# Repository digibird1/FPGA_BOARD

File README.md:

# FPGA_BOARD
Eagle design files of a two layer PCB for the ALTERA EP3C5E144 FPGA, including a FTDI USB2.0 controller, 2x 80 MSPS ADC, GPIO, JTAG, configuration FLASH 

https://www.altera.com/en_US/pdfs/literature/hb/cyc3/cyclone3_handbook.pdf

http://www.analog.com/media/en/technical-documentation/data-sheets/AD9057.pdf

http://www.ftdichip.com/Products/ICs/FT232H.htm

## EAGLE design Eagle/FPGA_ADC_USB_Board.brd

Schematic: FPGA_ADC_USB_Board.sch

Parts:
C1, C5, C7, C9, C11, C12, C13: 0.1u; C0805
C2, C3: 27p; C0805
C4, C8, C10: 47u; C0805
C6, C15: 0.1; C0805
C14: 10n; C0805
C16, C17, C18, C19, C20, C21, C22, C23, C24, C25, C26, C27, C28, C29, C30, C31, C32, C33, C34, C35, C36, C37, C38, C39, C41, C44, C47, C49, C53, C54, C55, C56, C59, C60, C61: 100n; C0805
C40, C42, C43, C45, C46, C48, C52: 10u; C0805
C50, C51, C57, C58: 100nF; C0805
C62: 1u; C0805
CONFIG_FLASH: EPCS-FALSH; SO08
D1, D2: BAV99; SOT23
D3, D4, D5: PMEG2010AEH; SOD123
EXT_5V: PINHD-1X2; 1X02
IC1: EP3C5E144-V2; EQFP144
IC2: 74LVC1G07DBV; SOT23-5
JTAG: PINHD-2X5; 2X05
L1, L2: 600R/0.5A; R0805
L3, L4, L5, L6, L7: MH2029-300Y; R0805
LED1: Yellow; R0805
LED2: Green; R0805
LED_1, LED_2, LED_3, LED_4: LED_ELED_0805; R0805
LS: 3.3V; SOT223
OSCILLATOR50_MHZ: 636L3I050M00000; OSZI_5X3.2
POWER_SELECT: PINHD-1X3; 1X03
Q1: 12MHz; QS
R1: 12k/1%; M0805
R2, R6, R7, R8: 10k; M0805
R3, R4: 0; M0805
R5: 2k; M0805
R9, R10: 470; M0805
R11: 27; M0805
R12: 24.9; R0805
R13, R14, R15, R17, R18: 10k; R0805
R16: 1k; R0805
R19, R30: 50Ohm; R0805
R20, R21, R22, R23, R24, R25: 0; R0805
R26, R27, R28, R29: 330; R0805
R31: 100k; R0805
R33: 120; R0805
S1: 10-XX; B3F-10XX
U$1: FT232H; LQFP48
U$2, U$6: AD9057; SSOP20
U$3: 93LC56; DIL-08
U$4: 2.5V; SOT223
U$5: 1.2V; SOT223
U$7: FPGA_GPIO_DE0; 2X20
U$8: NET_TIE; NET-TIE
X1: PN61729-S
X2, X3: BU-SMA-V

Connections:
1.2V: C16.1, C17.1, C18.1, C19.1, C20.1, C21.1, C22.1, C23.1, C36.1, C37.1, C48.1, IC1.5 (VCCINT), IC1.29 (VCCINT), IC1.37 (VCCD_PLL), IC1.45 (VCCINT), IC1.61 (VCCINT), IC1.78 (VCCINT), IC1.102 (VCCINT), IC1.109 (VCCD_PLL), IC1.116 (VCCINT), IC1.134 (VCCINT), U$5.2 (OUT), U$5.4 (OUT)
2.5V: C38.1, C39.1, C45.1, IC1.35 (VCCA), IC1.107 (VCCA), JTAG.4, R17.2, R18.2, R20.2, R22.2, R24.2, U$4.2 (OUT), U$4.4 (OUT)
3.3V: C4.1, C5.1, C11.1, C12.1, C13.1, C15.1, C24.1, C25.1, C26.1, C27.1, C28.1, C29.1, C30.1, C31.1, C32.1, C33.1, C34.1, C35.1, C42.1, C54.1, C59.1, CONFIG_FLASH.3 (VCC), CONFIG_FLASH.7 (VCC1), CONFIG_FLASH.8 (VCC2), D1.2 (C2), D2.2 (C2), IC1.17 (VCCIO), IC1.26 (VCCIO), IC1.40 (VCCIO), IC1.47 (VCCIO), IC1.56 (VCCIO), IC1.62 (VCCIO), IC1.81 (VCCIO), IC1.93 (VCCIO), IC1.117 (VCCIO), IC1.122 (VCCIO), IC1.130 (VCCIO), IC1.139 (VCCIO), IC2.5 (VCC), L1.1, L2.1, L6.1, LS.2 (OUT), LS.4 (OUT), R2.2, R6.2, R7.2, R8.2, R9.2, R10.2, R13.2, R14.2, R15.2, R31.2, U$1.12 (VCCIO), U$1.24 (VCCIO2), U$1.39 (VCCD), U$1.40 (VREGIN), U$1.46 (VCCIO3), U$2.15 (V_DD), U$3.8 (VCC), U$6.15 (V_DD), U$7.29 (3.3V)
5V: L3.1, L4.1, L5.1, L7.1, POWER_SELECT.2
5V_ANALOG: C52.1, C53.1, C55.1, C56.1, C60.1, C61.1, L7.2, U$2.5 (V_D1), U$2.8 (V_D2), U$6.5 (V_D1), U$6.8 (V_D2)
5V_EXT: D3.1 (A), POWER_SELECT.1
5V_USB: D5.2 (C), U$7.11 (5V), X1.1
ACBUS0: IC1.50 (IO50), U$1.21 (ACBUS0)
ACBUS1: IC1.44 (IO44), U$1.25 (ACBUS1)
ACBUS2: IC1.43 (IO43), U$1.26 (ACBUS2)
ACBUS3: IC1.38 (IO38), U$1.27 (ACBUS3)
ACBUS4: IC1.34 (IO34), R11.2
ACBUS6: IC1.33 (IO33), U$1.30 (ACBUS6)
ACBUS7: IC1.32 (IO32), U$1.31 (ACBUS7)
ACBUS8: IC1.31 (IO31), LED1.2 (C), U$1.32 (ACBUS8)
ACBUS9: IC1.30 (IO30), LED2.2 (C), U$1.33 (ACBUS9)
ADBUS0: IC1.65 (IO65), U$1.13 (ADBUS0)
ADBUS1: IC1.64 (IO64), U$1.14 (ADBUS1)
ADBUS2: IC1.60 (IO60), U$1.15 (ADBUS2)
ADBUS3: IC1.59 (IO59), U$1.16 (ADBUS3)
ADBUS4: IC1.54 (IO54), U$1.17 (ADBUS4)
ADBUS5: IC1.53 (IO53), U$1.18 (ADBUS5)
ADBUS6: IC1.52 (IO52), U$1.19 (ADBUS6)
ADBUS7: IC1.51 (IO51), U$1.20 (ADBUS7)
ADC1_CLK: IC1.113 (IO113), U$6.10 (ENCODE)
ADC1_D0: IC1.114 (IO114), U$6.20 (D0)
ADC1_D1: IC1.115 (IO115), U$6.19 (D1)
ADC1_D2: IC1.119 (IO119), U$6.18 (D2)
ADC1_D3: IC1.120 (IO120), U$6.17 (D3)
ADC1_D4: IC1.125 (IO125), U$6.14 (D4)
ADC1_D5: IC1.126 (IO126), U$6.13 (D5)
ADC1_D6: IC1.127 (IO127), U$6.12 (D6)
ADC1_D7: IC1.128 (IO128), U$6.11 (D7)
ADC2_CLK: IC1.112 (IO112), U$2.10 (ENCODE)
ADC2_D0: IC1.98 (IO98), U$2.20 (D0)
ADC2_D1: IC1.99 (IO99), U$2.19 (D1)
ADC2_D2: IC1.100 (IO100), U$2.18 (D2)
ADC2_D3: IC1.101 (IO101), U$2.17 (D3)
ADC2_D4: IC1.103 (IO103), U$2.14 (D4)
ADC2_D5: IC1.104 (IO104), U$2.13 (D5)
ADC2_D6: IC1.105 (IO105), U$2.12 (D6)
ADC2_D7: IC1.106 (IO106), U$2.11 (D7)
ADC_GND: C50.2, C55.2, C56.2, C57.2, C60.2, C61.2, R19.2, R30.2, U$2.4 (GND), U$2.9 (GND1), U$6.4 (GND), U$6.9 (GND1), U$8.NET1, X2.2, X2.3 (2), X2.4 (2), X2.5 (2), X3.2, X3.3 (2), X3.4 (2), X3.5 (2)
ASDI: CONFIG_FLASH.5 (ASDI), IC1.6 (IO6)
DATA: IC1.13 (IO13), R12.1
DCLK: CONFIG_FLASH.6 (DCLK), IC1.12 (DCLK)
FPGA_CLK: IC1.91 (CLK4), OSCILLATOR50_MHZ.3 (OUT)
GND: C1.2, C2.2, C3.2, C4.2, C5.2, C6.2, C7.2, C8.2, C9.2, C10.2, C11.2, C12.2, C13.2, C14.2, C15.2, C16.2, C17.2, C18.2, C19.2, C20.2, C21.2, C22.2, C23.2, C24.2, C25.2, C26.2, C27.2, C28.2, C29.2, C30.2, C31.2, C32.2, C33.2, C34.2, C35.2, C36.2, C37.2, C38.2, C39.2, C40.2, C41.2, C42.2, C43.2, C44.2, C45.2, C46.2, C47.2, C48.2, C49.2, C52.2, C53.2, C54.2, C59.2, C62.2, CONFIG_FLASH.4 (GND), D1.1 (A1), D2.1 (A1), D4.2 (C), IC1.19 (GND), IC1.21 (NCE), IC1.27 (GND), IC1.36 (GNDA), IC1.41 (GND), IC1.48 (GND), IC1.57 (GND), IC1.63 (GND), IC1.82 (GND), IC1.95 (GND), IC1.108 (GNDA), IC1.118 (GND), IC1.123 (GND), IC1.131 (GND), IC1.140 (GND), IC1.E (CENTER_GND_PLANE), IC2.3 (GND), JTAG.2, JTAG.10, LED_1.2 (C), LED_2.2 (C), LED_3.2 (C), LED_4.2 (C), LS.1 (GND), OSCILLATOR50_MHZ.2 (GND), R1.1, R16.2, R21.1, R23.1, R25.1, S1.3, S1.4 (P1), U$1.4 (AGND1), U$1.9 (AGND2), U$1.10 (GND1), U$1.11 (GND2), U$1.22 (GND3), U$1.23 (GND4), U$1.35 (GND5), U$1.36 (GND6), U$1.41 (AGND3), U$1.42 (TEST), U$1.47 (GND7), U$1.48 (GND8), U$2.1 (PWRDN), U$2.16 (GND2), U$3.5 (GND), U$4.1 (GND), U$5.1 (GND), U$6.1 (PWRDN), U$6.16 (GND2), U$7.12 (GND), U$7.30 (GND2), U$8.NET2, X1.4
GPIO1_CLKIN0: IC1.88 (CLK7), U$7.1 (CLKIN0)
GPIO1_CLKOUT0: IC1.85 (IO85), U$7.19 (CLKOUT0)
GPIO1_CLKOUT1: IC1.87 (IO87), U$7.21 (CLKOUT1)
GPIO1_D0: IC1.66 (IO66), U$7.2 (D0)
GPIO1_D1: IC1.67 (IO67), U$7.4 (D1)
GPIO1_D2: IC1.68 (IO68), U$7.5 (D2)
GPIO1_D3: IC1.69 (IO69), U$7.6 (D3)
GPIO1_D4: IC1.70 (IO70), U$7.7 (D4)
GPIO1_D5: IC1.71 (IO71), U$7.8 (D5)
GPIO1_D6: IC1.72 (IO72), U$7.9 (D6)
GPIO1_D7: IC1.73 (IO73), U$7.10 (D7)
GPIO1_D8: IC1.74 (IO74), U$7.13 (D8)
GPIO1_D9: IC1.75 (IO75), U$7.14 (D9)
GPIO1_D10: IC1.76 (IO76), U$7.15 (D10)
GPIO1_D11: IC1.77 (IO77), U$7.16 (D11)
GPIO1_D12: IC1.79 (IO79), U$7.17 (D12)
GPIO1_D13: IC1.84 (IO84), U$7.18 (D13)
GPIO1_D14: IC1.86 (IO86), U$7.20 (D14)
LED1: IC1.1 (IO1), R26.2
LED2: IC1.2 (IO2), R27.2
LED3: IC1.3 (IO3), R28.2
LED4: IC1.4 (IO4), R29.2
MSEL0: IC1.94 (MSEL0), R20.1, R21.2
MSEL1: IC1.96 (MSEL1), R22.1, R23.2
MSEL2: IC1.97 (MSEL2), R24.1, R25.2
unnamed: C9.1, C10.1, L1.2, U$1.8 (VPLL)
unnamed: CONFIG_FLASH.2 (DATA), R12.2
unnamed: C1.1, U$1.37 (VCCA)
unnamed: R1.2, U$1.5 (REF)
unnamed: C6.1, U$1.38 (VCCCORE)
unnamed: C2.1, Q1.1, U$1.1 (XCSI)
unnamed: C3.1, Q1.2, U$1.2 (XCSO)
unnamed: C14.1, R2.1, U$1.34 (RESET)
unnamed: R4.1, U$1.7 (DP)
unnamed: IC1.9 (NSTATUS), R13.1
unnamed: D1.3 (COM), R3.2, X1.2
unnamed: R3.1, U$1.6 (DM)
unnamed: C7.1, C8.1, L2.2, U$1.3 (VPHY)
unnamed: D2.3 (COM), R4.2, X1.3
unnamed: IC1.14 (NCONFIG), R14.1
unnamed: IC1.92 (CONF_DONE), R15.1
unnamed: C40.1, C41.1, L3.2, LS.3 (IN)
unnamed: C43.1, C44.1, L4.2, U$4.3 (IN)
unnamed: C46.1, C47.1, L5.2, U$5.3 (IN)
unnamed: D3.2 (C), EXT_5V.1
unnamed: D4.1 (A), EXT_5V.2
unnamed: D5.1 (A), POWER_SELECT.3
unnamed: C49.1, L6.2, OSCILLATOR50_MHZ.1 (OE), OSCILLATOR50_MHZ.4 (VCC)
unnamed: C51.2, U$6.6 (BIAS_OUT), U$6.7 (AIN)
unnamed: C50.1, U$6.2 (VREF_OUT), U$6.3 (VREF_IN)
unnamed: C51.1, R19.1, X2.1
unnamed: C58.2, U$2.6 (BIAS_OUT), U$2.7 (AIN)
unnamed: R6.1, U$1.45 (EECS), U$3.1 (CS)
unnamed: R7.1, U$1.44 (EECLK), U$3.2 (CLK)
unnamed: R5.2, U$1.43 (EEDATA), U$3.3 (DI)
unnamed: R5.1, R8.1, U$3.4 (DO)
unnamed: C57.1, U$2.2 (VREF_OUT), U$2.3 (VREF_IN)
unnamed: C58.1, R30.1, X3.1
unnamed: LED_1.1 (A), R26.1
unnamed: LED_2.1 (A), R27.1
unnamed: LED1.1 (A), R9.1
unnamed: LED2.1 (A), R10.1
unnamed: LED_3.1 (A), R28.1
unnamed: R11.1, U$1.28 (ACBUS4)
unnamed: LED_4.1 (A), R29.1
unnamed: IC2.4 (O), R33.1
unnamed: C62.1, IC2.2 (I), R31.1, S1.1 (S), S1.2 (S1)
NCS: CONFIG_FLASH.1 (NCS), IC1.8 (IO8)
PB0: IC1.133 (IO133), R33.2
TCK: IC1.16 (TCK), JTAG.1, R16.1
TDI: IC1.15 (TDI), JTAG.9, R18.1
TDO: IC1.20 (TDO), JTAG.3
TMS: IC1.18 (TMS), JTAG.5, R17.1
USB_CLK: IC1.25 (CLK3), U$1.29 (ACBUS5)

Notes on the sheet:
3.3V
Here should be some esd protection!!!
Pull ACBus4 High if in FIFO Mode
VCCINT
VCCIO
VCCA
VCCD_PLL
Oscillator 636L3I050M00000
Which Pin is the Oszi?
Power-Down Function Select; Logic High for Power-Down Mode (Digital Outputs Go to High Impedance State).
What about memour can be used as a buffer
Put resistor close to flash
Configuration Scheme Connect MSEL 2/1/0 to 0/1/0 where 0 is GND and 1 is VCCA
Add some LEDs
What about BAT double diode
Make sure to connect the ADC and other to the PLL clk out of the FPGA
Connect the 50MHz clock to more pins? The 60MHz clock of the USB interface into a clock pin?
CHeck that we hav a good ground under the FPGA and not just a single connection!
Check that voltage is evenly distributed And ground is evenly connected as well
Place vias in analog GND
Pushbutton
The CLKOUT are not connected to the CLK Network!!!

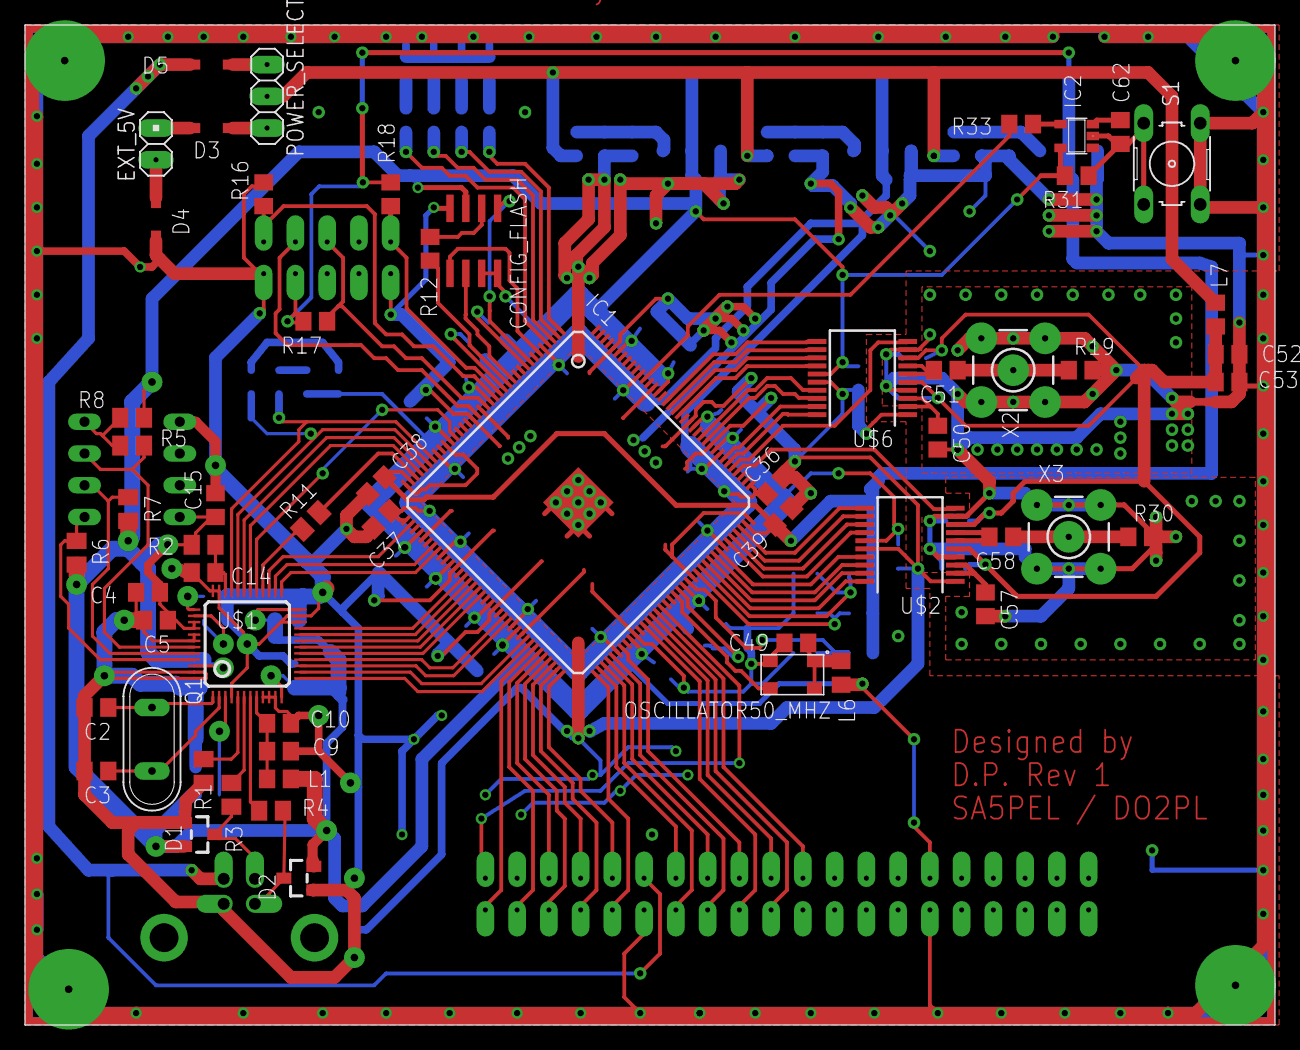
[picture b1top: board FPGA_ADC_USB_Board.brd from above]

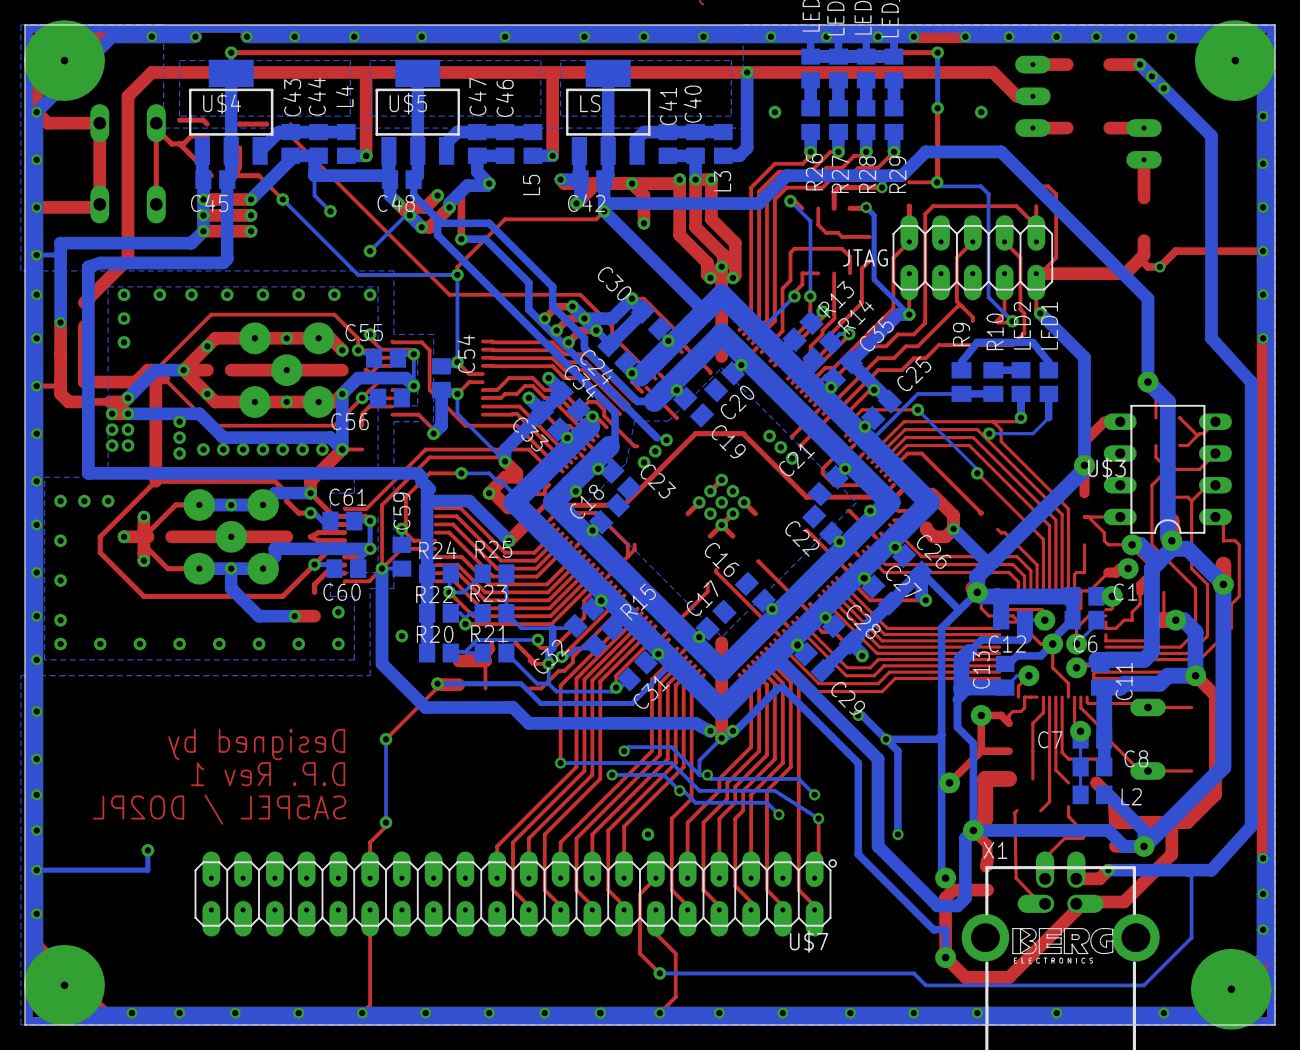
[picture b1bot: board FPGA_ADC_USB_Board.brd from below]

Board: 2 copper layers, 100.0 x 80.0 mm, 133 parts (74 on the bottom side), 122 nets.

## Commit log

2015-04-01 Eagle PCB files
2015-04-01 Create README.md
    Eagle design files of a two layer PCB for the ALTERA EP3C5E144 FPGA, including a FTDI USB2.0 controller, 2x 80 MSPS ADC, GPIO, JTAG, configuration FLASH
    https://www.altera.com/en_US/pdfs/literature/hb/cyc3/cyclone3_handbook.pdf
    http://www.analog.com/media/en/technical-documentation/data-sheets/AD9057.pdf
    http://www.ftdichip.com/Products/ICs/FT232H.htm
